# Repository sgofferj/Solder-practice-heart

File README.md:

# Solder practice PCB for kids

License: CC-BY-SA 4.0

I designed this PCB to teach my 6 years old son soldering and some electronics basics. The cutout on top fits a standard ID card clip, so the PCB can be worn as some kind of brooch if desired.

The resistors need to be calculated according to the LED color and the desired current. Red LEDs running at 10mA would be 150R.

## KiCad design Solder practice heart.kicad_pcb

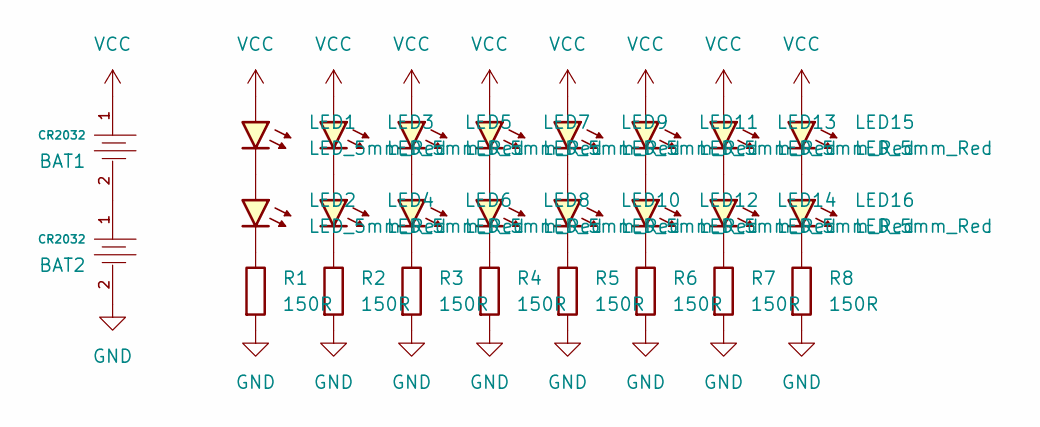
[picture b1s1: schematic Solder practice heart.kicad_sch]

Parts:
BAT1, BAT2: CR2032; BAT-TH_BS-07-A1BJ001; Part BS-07-A1BJ001; LCSC C2979167
LED1, LED2, LED3, LED4, LED5, LED6, LED7, LED8, LED9, LED10, LED11, LED12, LED13, LED14, LED15, LED16: LED_5mm_Red; LED_D5.0mm
R1, R2, R3, R4, R5, R6, R7, R8: 150R; R_Axial_DIN0207_L6.3mm_D2.5mm_P10.16mm_Horizontal

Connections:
GND: BAT2.2, R1.1, R2.1, R3.1, R4.1, R5.1, R6.1, R7.1, R8.1
unnamed: BAT1.2, BAT2.1
unnamed: LED1.1 (K), LED2.2 (A)
unnamed: LED2.1 (K), R1.2
unnamed: LED3.1 (K), LED4.2 (A)
unnamed: LED4.1 (K), R2.2
unnamed: LED5.1 (K), LED6.2 (A)
unnamed: LED6.1 (K), R3.2
unnamed: LED7.1 (K), LED8.2 (A)
unnamed: LED8.1 (K), R4.2
unnamed: LED9.1 (K), LED10.2 (A)
unnamed: LED10.1 (K), R5.2
unnamed: LED11.1 (K), LED12.2 (A)
unnamed: LED12.1 (K), R6.2
unnamed: LED13.1 (K), LED14.2 (A)
unnamed: LED14.1 (K), R7.2
unnamed: LED15.1 (K), LED16.2 (A)
unnamed: LED16.1 (K), R8.2
VCC: BAT1.1, LED1.2 (A), LED3.2 (A), LED5.2 (A), LED7.2 (A), LED9.2 (A), LED11.2 (A), LED13.2 (A), LED15.2 (A)

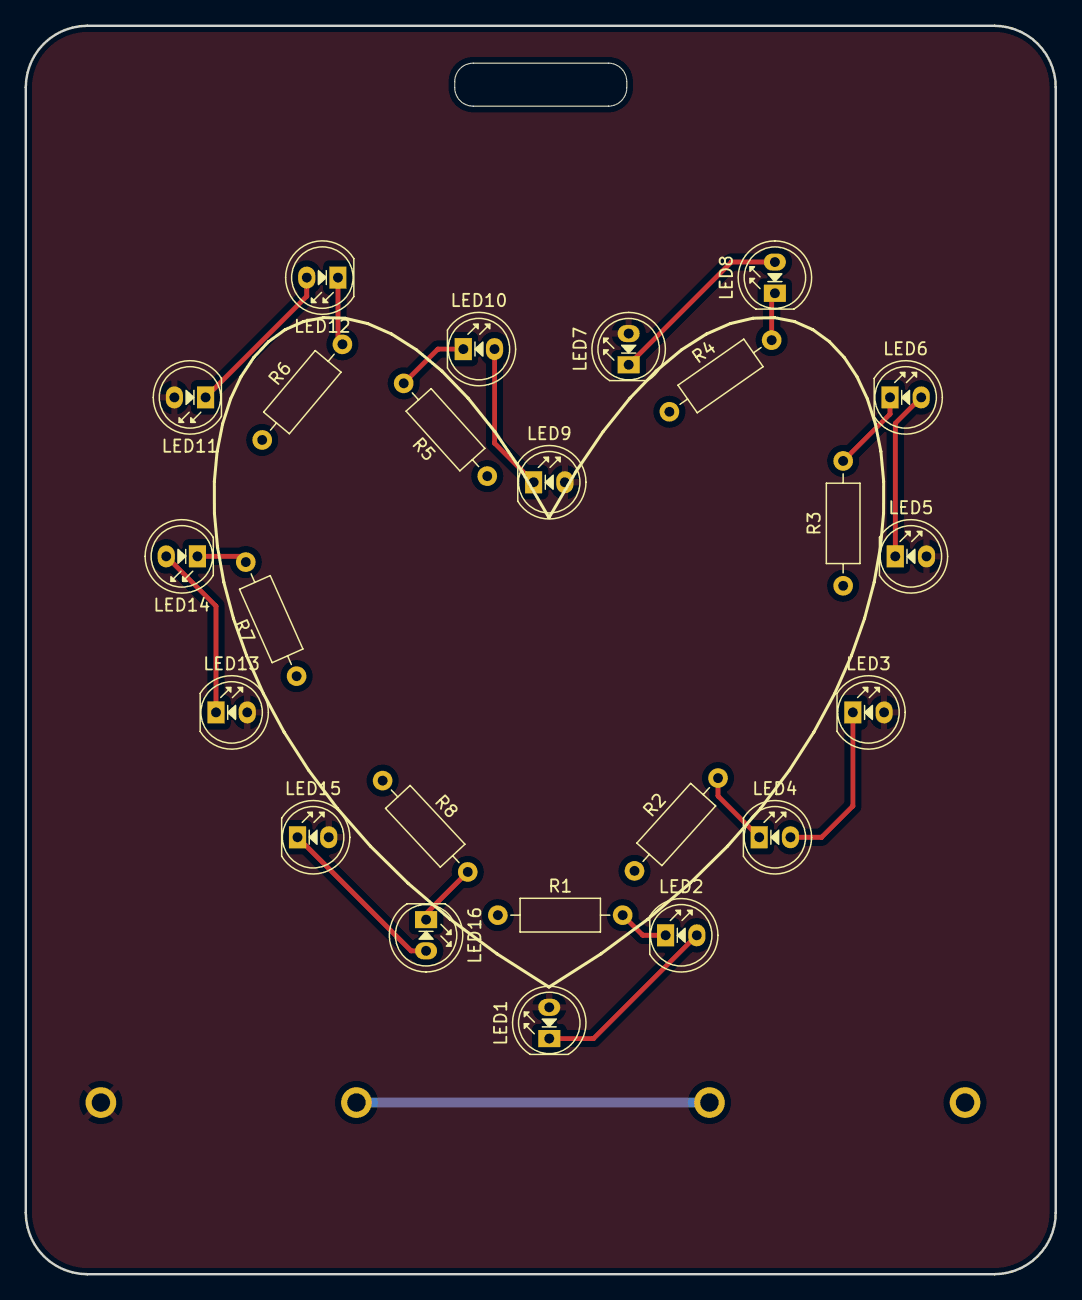
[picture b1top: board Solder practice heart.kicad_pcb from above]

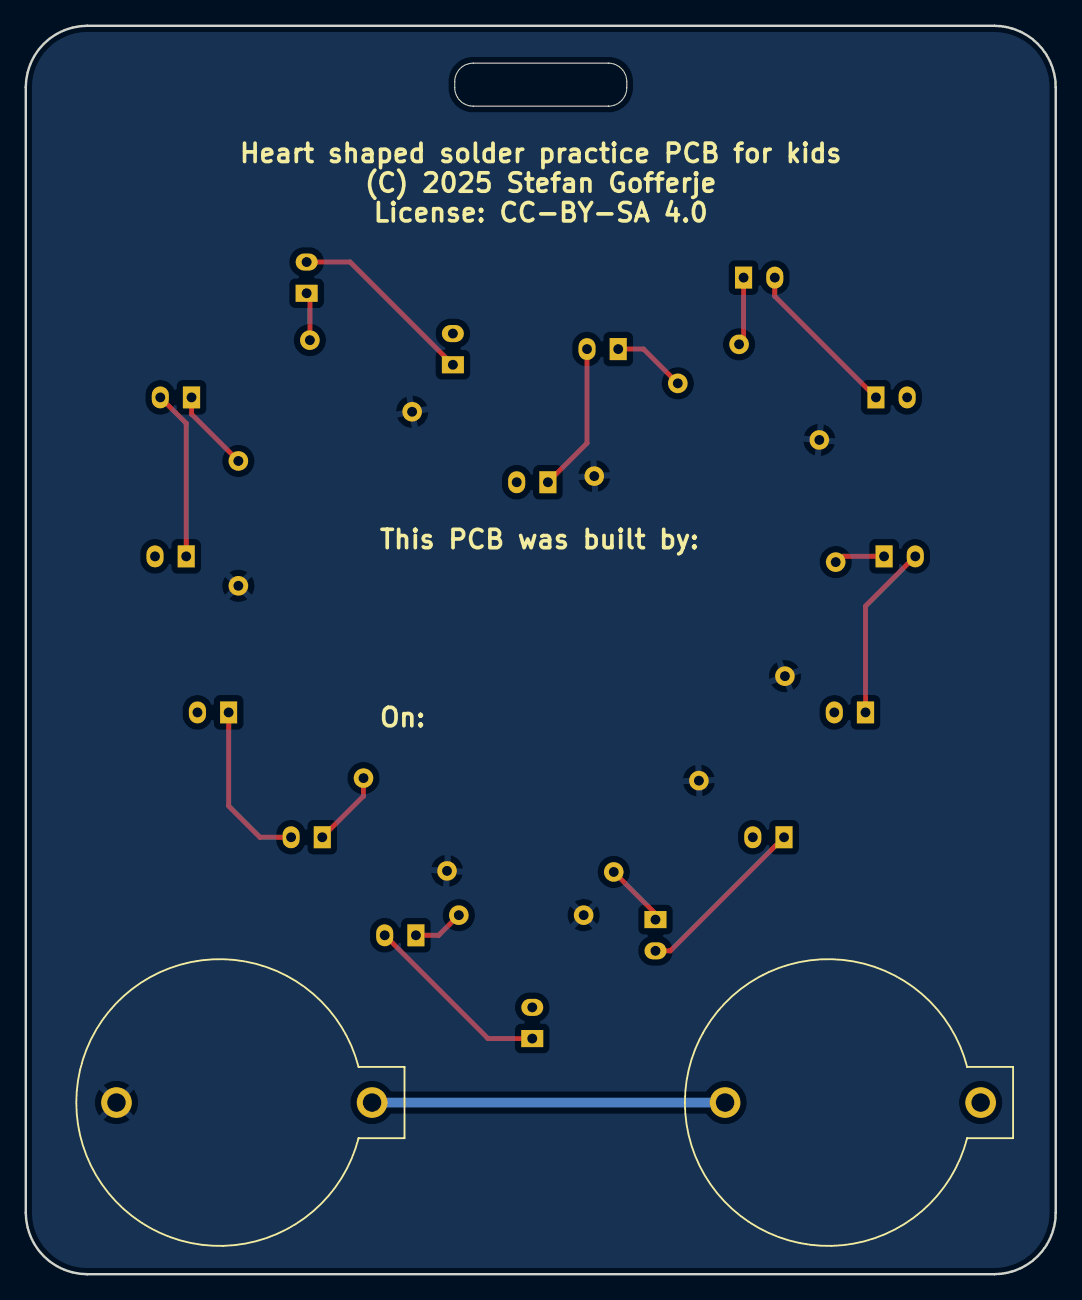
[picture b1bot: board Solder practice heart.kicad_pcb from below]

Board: 2 copper layers, 83.8 x 101.6 mm, 26 parts (2 on the bottom side), 19 nets.

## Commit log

2025-02-15 Correct image link
2025-02-15 Use both images
2025-02-15 Redone PCB, added Gerbers
2025-02-15 Readme
2025-02-15 Forgot one track...
2025-02-15 Readme typo
2025-02-16 Add license text to PCB silkscreen Update Readme
2025-02-16 Update pictures

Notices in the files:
Solder practice heart.kicad_pcb:
(C) 2025 Stefan Gofferje
License: CC-BY-SA 4.0
